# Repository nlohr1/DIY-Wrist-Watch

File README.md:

# DIY-Wrist-Watch
### Small 3D-Printed OLED-Clock with RTC and ATmega328-chip, based on Arduino-code

Small OLED-Clock with the small **8-pin** Real-Time chip DS3231**MZ** and the commonly known (Arduino) ATmega328 uController chip,
in conjunction with a 128x64px OLED-Display (SSD1306-chip) - displaying Date, Time, (Battery)-Voltage and Skin-Temperature.

----
**OLED-Clock Case & Foto:**  

**Schematic:**  

**PCB-Layout:**  
  
Att: Push-Buttons soldered on PCB-background! - Female Socket-headers (yellow bushings) soldering: see "OLED-Clock-6-nl_Case.png"!

----
### Partlist (BOM) for "OLED-Clock-6-nl.sch":  
<pre><b><code>Qty.  Components      Value          Description                                        Package</code></b><code>
1x     C1              2,2uF          Capacitor, SMD                                     C0603
3x     C2,C3,C4        1uF            Capacitor, SMD                                     C0603
5x     C5,C6,C7,C8,C9  100n           Capacitor, SMD                                     C0603
2x     D1,D2           BAS40-05(W)    Dual-Schottky-Diode, low-leakage (1uA), SMD        SOT23 (-323-R)
1x     IC1             ATMEGA328P     8-bit Microcontroller (4x8 = 32 Pin), SMD          TQFP32-08
1x     IC2             DS3231MZ       RTC Real-Time Clock (8-Pin), SMD                   SO08
1x     JP1             AVR-ISP-6      AVR ISP-6 Serial Programming Header                AVR-ISP-6
1x     LED1            cool-white     Osram-LED-Duris-E3, 2.240mcd, 3V/30mA, SMD-3014    Chipled 1206
1x     LED2            blue           High-Efficiency LED, 2.5V-forward-voltage, SMD     Chipled 0805
1x     MD1             OLED-Display   I2C OLED-Module 0.96", (SSD1306 chip), SMD         128x64px
1x     R1              10k            Resistor, SMD                                      R0603
1x     R2              33R            Resistor, SMD                                      R0603
4x     R3,R4,R5,R6     100k           Resistor, SMD                                      R0603
2x     R7,R8           1k             Resistor, SMD                                      R0603
2x     S1,S2           Push-Button    Micro Tactile Switch 12V, 50mA, SMD                3.7x6x2.5mm
1x     T1              FDC6327C       Dual N+P-Channel Mosfet, SMD                       SOT23-6
14x    Socket          1x40 Pin       Female Socket-header, short (L:7.0mm, hole:0.6mm)  RM:2,54mm
1x     Board           FR4 #0.8mm     Mainboard, 2-layer (Cu 35um), #0.8mm               27.3x26.9mm
1x     Case            PLA or PETG    3D printed, 0.13mm layer-height, 100% Infill       31x36x10mm
1x     Lid             PLA or PETG    Bottom-Lid, case-latching                          29x28x2mm
1x     Strap           Inox           20mm Quick Release Milanese Mesh Watch Band        width: 20mm
2x     Wire            Inox or Steel  Inox or Galvanized Steel-Wires ø1.2mm              L: 29mm
2x     Bushing         Inox or Steel  Inox- or Brass-Bushing, ø1.8/1.5 mm                L: 20mm
</code></pre>   

----
Both, Micro-Processor and OLED are switched-on at Button-press, and off/disconnected from Battery **per hardware** (Schmitt-Trigger Transistor-circuit) after about 8 seconds, so that the only remaining consumption comes from RTC-chip (in stand-by-mode), consuming less than 1uA.  

I resigned to use the uControllers software-"power-down"-function, because this does not disconnect the OLED-display(chip) and other chips on board from Battery, which are causing additional power-consumptions.  
Current-Leakages are minimized through the double-mosfet FDC6237 (small Gate-Capacitances and Gate Threshold Voltages with 1-2V) and two double-diodes (BAS40-05W) with very small leakage-currents of 20nA.  
With this configuration the CR2032-Lithium-Battery lasts more than 2 years (proved! - using the clock-display about 10 times/day).

The Clock additionally provides a calendar, displaying the actual month(days) and a relatively bright Flashlight-LED, consuming only about 10mA.

Two Buttons are handling the Display-"On", Calendar, FlashLight-On/Off and Set/Reset of the Clock, meanwhile Display-"Off" is done automatically after 8 seconds.
The code is subdivided in several sections, with jump-markers: §0, §1, §2... explained in the code-head.  
I commented every line of the software, so it's possible to understand and modify it (at your own "risk")...  
File "OLED-Watch-6-nl-Manual.txt" provides a short user-manual list.  

The Software program-code (Arduino-based C++) is flashed through an ISP-Programmer to the ATmega328-Chip - **without bootloader**, to save start-time.  
To flash the chip I use the known **avrdude** as command-line-program, flashing the (Arduino-compiled) resulting hex-file with an ISP-Programmer (USBasp or similar), this programmer connected on one side through USB to my Notebook and on the other through a 6-pole ISP-Connector-Socket to the 6 Clock-pcb-board bushings.  

Avrdude command lines to flash the code into the ATmeag328-chip are explained also on the end of the program-file:  

> **"OLED-Clock-w-Led-and-Calendar.ino"** *(open/edit this file with a Text-Editor like Notepadd++)*  
> &nbsp; or directly in the Arduino-GUI, then compile it and

use the .hex-result in following command-line:  
> avrdude.exe -v -V -p m328p -c usbasp -B10 -e -D -U flash:w:OLED-Clock-w-Led-and-Calendar.ino.hex:i

The Case, Lid and battery-Holder are 3D-Printed with 0.13mm Layer-height and 100% Infill (PLA: 210°C / 60°C). I provided .stl-files of case, lid and battery-holder, also the corresponding .gcode-files for a medium 3D-Printer (bed-size about: 220 x 220 mm), as beeing Prusa-MK3 or similar printers like Anycubic-Pro, etc. (negligible differences in bed-sizes).

- Sliced with Prusa-Slicer - my profile-file: "prusaslicer_config.ini" - you may load it with the Hotkey [Ctr+L] into the Prusa-Slicer...  

- PCB schematic and Layout: Eagle 7.4
- Prototype etched with 0.8mm FR4-board with Toner-Direct methode (2 layers: first CNC-drilled the FR-material, (blank/fine-sanded + cleaned with acetone), then transferred the layout with toner-transfer-paper: 2 layers fixed/congruented on the 4 outer-edges/holes with ø0.4mm needles, this needles exchanged with ø0,4mm clamping-wire, fixing the paper on the FR4-board also with kapton-band on top and both sides, this "sandwitch" then toner-laminated with a 200°C modified laminator, etched in sodium persulfate at 70-80°C (etching-result in ≈ 5-10 min) + finally hot-tinned both sides with a flat soldering iron.
---

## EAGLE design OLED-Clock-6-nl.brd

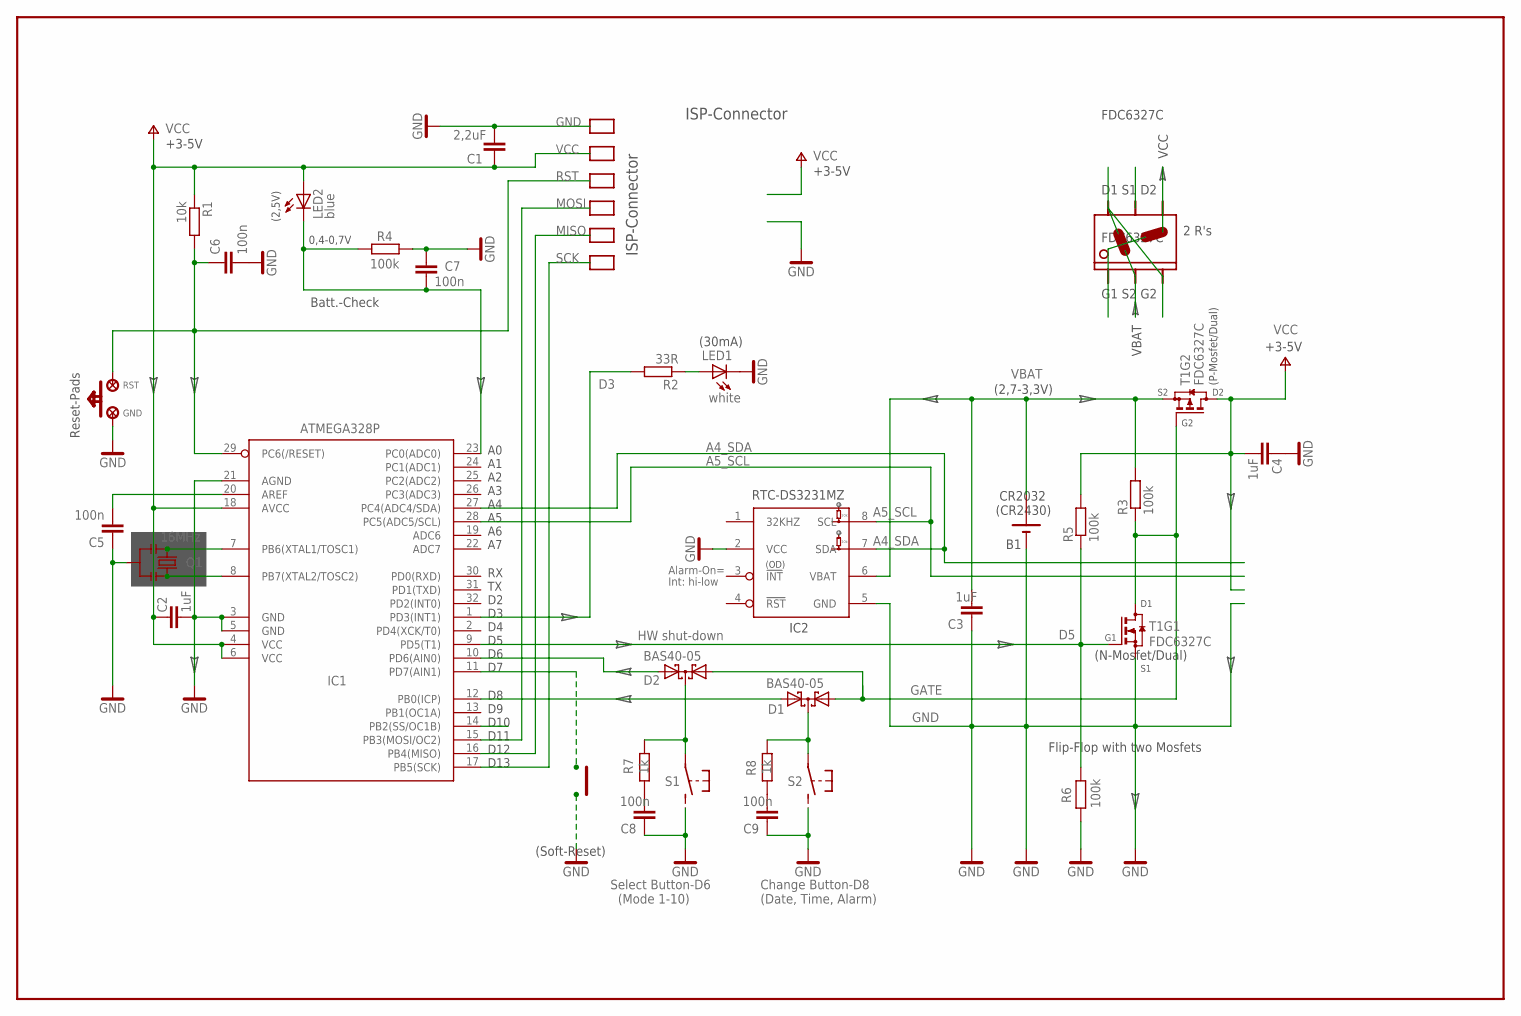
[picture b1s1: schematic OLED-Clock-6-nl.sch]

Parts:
C1: 2,2uF; C0603
C2, C3, C4: 1uF; C0603
C5, C6, C7, C8, C9: 100n; C0603
D1, D2: BAS40-05; SOT23
GND: LSP20
IC1: ATMEGA328P; TQFP32-08
IC2: DS3231MZ; SO08
LED1: white; CHIPLED_1206
LED2: blue; CHIPLED_0805
R1: 10k; R0603
R2: 33R; R0603
R3, R4, R5, R6: 100k; R0603
R7, R8: 1k; R0603
RST: LSP20
T1: FDC6327C; SOT23-6

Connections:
A0: C7.1, IC1.23 (PC0(ADC0)), LED2.C, R4.1
A4_SDA: IC1.27 (PC4(ADC4/SDA)), IC2.7 (SDA)
A5_SCL: IC1.28 (PC5(ADC5/SCL)), IC2.8 (SCL)
D3: IC1.1 (PD3(INT1)), R2.2
D5: IC1.9 (PD5(T1)), R5.1, R6.2, T1.1 (G)
D6: D2.2 (A2), IC1.10 (PD6(AIN0))
D7: IC1.11 (PD7(AIN1))
GATE: D1.1 (A1), D2.1 (A1), R3.1, T1.3 (G), T1.6 (D)
GND: C1.2, C2.2, C3.1, C4.1, C5.1, C6.2, C7.2, C8.1, C9.1, GND.P$1, IC1.3 (GND), IC1.5 (GND), IC1.21 (AGND), IC2.2 (VCC), IC2.5 (GND), LED1.C, R4.2, R6.1, T1.5 (S)
MISO: IC1.16 (PB4(MISO))
MOSI: IC1.15 (PB3(MOSI/OC2))
unnamed: D2.3 (C), R7.2
unnamed: C5.2, IC1.20 (AREF)
unnamed: D1.3 (C), R8.2
unnamed: D1.2 (A2), IC1.12 (PB0(ICP))
unnamed: LED1.A, R2.1
unnamed: C8.2, R7.1
unnamed: C9.2, R8.1
RST: C6.1, IC1.29 (PC6(/RESET)), R1.2, RST.P$1
SCK: IC1.17 (PB5(SCK))
VBAT: C3.2, IC2.6 (VBAT), R3.2, T1.2 (S)
VCC: C1.1, C2.1, C4.2, IC1.4 (VCC), IC1.6 (VCC), IC1.18 (AVCC), LED2.A, R1.1, R5.2, T1.4 (D)
X1: IC1.7 (PB6(XTAL1/TOSC1))
X2: IC1.8 (PB7(XTAL2/TOSC2))

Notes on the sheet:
RTC-DS3231MZ
A0 A1 A2 A3 A4 A5 A6 A7
RX TX D2 D3 D4 D5 D6 D7
D8 D9 D10 D11 D12 D13
ISP-Connector
Select Button-D6 (Mode 1-10)
Change Button-D8 (Date, Time, Alarm)
HW shut-down
Batt.-Check
CR2032 (CR2430)
(P-Mosfet/Dual)
0,4-0,7V
IC2
(N-Mosfet/Dual)
(2,5V)
+3-5V
Alarm-On= Int: hi-low
Flip-Flop with two Mosfets
10k
(30mA)
(Soft-Reset)
(OD)
16MHz
G1 S2 G2
D1 S1 D2
FDC6327C
2 R's
VCC
VBAT
Reset-Pads
(2,7-3,3V)

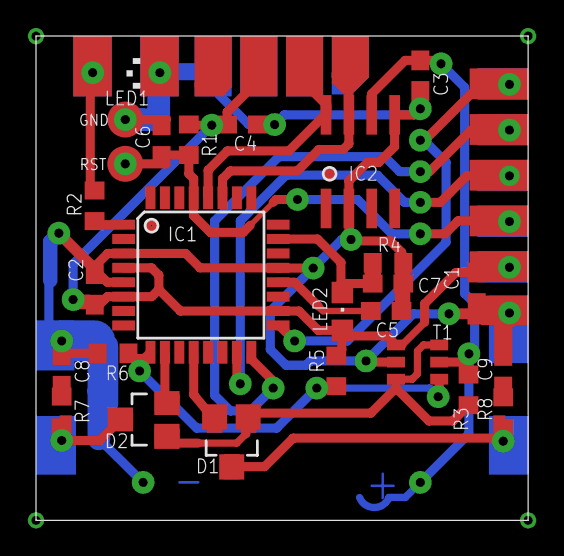
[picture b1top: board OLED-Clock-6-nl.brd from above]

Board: 2 copper layers, 27.3 x 26.9 mm, 26 parts (0 on the bottom side), 18 nets.
